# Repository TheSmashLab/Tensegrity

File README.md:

# Tensegrity
All code and any additional documents regarding research in the Tensegrity projects

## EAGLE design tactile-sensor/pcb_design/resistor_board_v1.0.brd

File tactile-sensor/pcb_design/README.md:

# Overview

This project was made by members of the Robotics and Dynamics Lab at Brigham Young University. This directory contains all of the necessary instructions and files for the custom PCB's we designed for reading force data from up to eight 16x64 fabric tactile sensor arrays (or a total of 8192 force readings) at up to 80sps. These boards, in combination with an Arduino Due, enable the use of ROS to read large amounts of tactile data.

These PCBs were designed using Autodesk EAGLE, then later using Fusion 360. The corresponding board, and schematic files are found in this directory, as well as the CAM outputs. These are easy enough to import into Fusion 360.

We used JLCPCB to print out PCBs.

There are three pcbs in this directory: a tactile sensor master board that is a shield for the Arduino Due, a tactile sensor slave board that is mounted next to and attached to each 16x64 sleeve sensor array, and a resistor board that is an add-on to the slave board.
To understand the design behind these PCB's, espessially the slave PCB which is the most technical, I suggest reading the Tactile_Sleeve_Notes.pdf file in the resources folder.

---
# Tactile Sensor Master Board

## Bill of Materials for each Board

| Qty |  Cost  | Device                          | Parts                                                   | Description                                 | PURCHASE_URL |
|-----|--------|---------------------------------|---------------------------------------------------------|---------------------------------------------|--------------|
| 2   | $0.10  | 3-pin Male Header               | SV1, SV2                                                | Decide termination and power source         | NA           |
| 1   | $0.20  | 5-pin Female Header             | SV3                                                     | Plug in external 3.3V buck converter        | NA          |
| NA  | $1.00  | Male Header Pins                |                                                         | Headers needed to put the shield on the due | NA          |
| 8   | $0.35  | 2-pin Male Molex Connector      | CS1, CS2, CS3, CS4, CS5, CS6, CS7, CS8                  | For CS pins                                 | [link](https://www.mouser.com/ProductDetail/Molex/171856-0002?qs=s7UCm7gO1bYKeEMrirBzyw%3D%3D)             |
| 1   | $4.95  | 8-pin Dip Switch                | J1                                                      | Dip switch for selecting sleeve to read     | [link](https://www.mouser.com/ProductDetail/Omron-Electronics/A6E-8104-N?qs=vyIerDHf/mloJqQ30NZRaQ%3D%3D)             |
| 2   | $1.00  | Ethernet port                   | CHAIN_1, CHAIN_2                                        | Used for daisy-chaining slave devices       | [link](https://www.mouser.com/ProductDetail/TE-Connectivity-AMP/5555164-4?qs=BcfjnG7NVaVPSt3aHUi1SQ%3D%3D)           |
| 1   | $1.02  | 200 Ohm Potentiometer           | R1                                                      | Used for terminating data line              | [link](https://www.mouser.com/ProductDetail/Bourns/3362P-1-201LF?qs=sGAEpiMZZMtC25l1F4XBU4KpuikCFD1JVjzxlorewD8%3D)              |
| 1   | $15.95 | External 3.3V Buck Converter    |                                                         | Powers all of the sensors                   | [link](https://www.pololu.com/product/3781)             |

The total price per board (including printing the pcb) is about $40 (parts are $28.02 and JLCPCB charges about $20 for 5 copies of the pcb, plus shipping and tax). Note that there are fairly significant bulk discounts for many of these parts. 

## Schematic

NOTE: there is a PDF version of the schematic in this directory if greater resolution is needed.

## Layout

## Setup

There are a few things that you can physically change on this board. First, the 8-channel dip switch is used to tell the arduino which sensors it should report. If the arduino due is running the tactile_sensors_reporter.ino file, it will read which switches are flipped on and only report the sensors that correspond to those switches. The slave select pins that correspond to each switch are labelled (CS1, CS2, etc.). Use a wire to connect the correct CS pin on the master to the SS pin on the slave device.

Second, there are three male header pins next to the data termination potentimeter. The data line should be terminated using the potentiometer set to 120 ohms (or a tuned value) if only one chain is being used. If both chains are being used, then the line should not be terminated.

Lastly, there is another set of three male header pins with the words EXT and ARD. This will determine if you want to power the sensors from the external buck converter or the arduino. Only power up to two sensors using the arduino. In any other case, use the external buck converter.

---
# Tactile Sensor Slave Board with Add-on Board

## Bill of Materials

| Qty | Cost  | Device                     | Parts                                                       | Description                                   | Purchase Link                                                                                                                                                                                                                                                                                                                                                                                                                                             |
|-----|-------|----------------------------|-------------------------------------------------------------|-----------------------------------------------|-----------------------------------------------------------------------------------------------------------------------------------------------------------------------------------------------------------------------------------------------------------------------------------------------------------------------------------------------------------------------------------------------------------------------------------------------------------|
| 5   | $0.89 | 16-channel Analog Mux      | CMUX, AMUX_1, AMUX_2, AMUX_3, AMUX_4                        | Multiplexers for switching between sensors    | [link](https://www.mouser.com/ProductDetail/Texas-Instruments/CD74HC4067SM96?qs=JHHQeKcAU3DyfvAOSRLjhQ%3D%3D)                                                                                                                                                                                                                                                                                                                                                                                                                                                          |
| 1   | $0.96 | 4-channel Analog Mux       | AMUX_0                                                      | Multiplexer for switching between sensors     | [link](https://www.mouser.com/ProductDetail/Texas-Instruments/TMUX1204DGSR?qs=EBDBlbfErPw42Q0DdvAwUg%3D%3D) |
| 1   | $12.76| SPI-enabled 12-bit ADC     | ADC                                                         | ADC for reading voltage divider               | [link](https://www.mouser.com/ProductDetail/Analog-Devices-Maxim-Integrated/MAX11103AUB%2b?qs=mzcOS1kGbgdW3dlgSnprJw%3D%3D) |
| 1   | $1.38 | 12-bit Binary Counter      | SW                                                          | Counter for triggering MUX's based on clock   | [link](https://www.mouser.com/ProductDetail/Texas-Instruments/SN74LV4040AD?qs=UG/8xqv/6WeL19NQ6cIFrg%3D%3D) |
| 2   | $1.00 | Ethernet port              | INPUT, OUTPUT                                               | Connection for daisy-chain                    | [link](https://www.mouser.com/ProductDetail/TE-Connectivity-AMP/5555164-4?qs=BcfjnG7NVaVPSt3aHUi1SQ%3D%3D) |
| 4   | $0.60 | 2x8-pin Male Header        | ASEL_1, ASEL_2, ASEL_3, ASEL_4                              | For plugging in fabric sensor ribbon cable    | [link](https://www.mouser.com/ProductDetail/Amphenol-FCI/67996-416HLF?qs=zDLUbuhEZ18YJlcRJvn0zg%3D%3D) |
| 1   | $1.86 | 2x8-pin Long Male Header   | CSEL                                                        | For plugging in fabric sensor ribbon cable    | [link](https://www.mouser.com/ProductDetail/Samtec/HTSW-108-10-T-D?qs=%252BZP6/%252BtExtB9K2tO%252BdFStQ%3D%3D) |
| 3   | $0.28 | SPI-enabled 12-bit ADC     | SV1, SV2, ADC_SEL                                           | Turn on termination and choose ADC channel    | [link](https://www.mouser.com/ProductDetail/Amphenol-FCI/68000-403H?qs=eanFghet1JNqC/0Iz%252BuUPw%3D%3D) |
| 3   | $1.02 | 200 Ohm Potentiometer      | R1, R2, R5                                                  | Used for terminating communication lines      | [link](https://www.mouser.com/ProductDetail/Bourns/3362P-1-201LF?qs=sGAEpiMZZMtC25l1F4XBU4KpuikCFD1JVjzxlorewD8%3D)              |
| 1   | $0.89 | 3k Ohm Potentiometer       | R4                                                          | Used as the know half of the voltage divider  | [link](https://www.mouser.com/ProductDetail/Bourns/3362P-1-302LF?qs=sGAEpiMZZMtC25l1F4XBUxCk7s1FufIVD8TlfNkTc8c%3D) |
| 1   | $0.36 | 2-pin Male Molex Connector | SS                                                          | Connection for CS on slave                    | [link](https://www.mouser.com/ProductDetail/Molex/171857-0002?qs=vOeJqewp7jDZ/eRg0MxvZQ%3D%3D) |
| 10  | $0.29 | Blue 3.3V LED              | LED1, LED2, LED3, LED4, LED5, LED6, LED7, LED8, LED9, LED10 | Used to debug clock, display current sensor   | [link](https://www.mouser.com/ProductDetail/Stanley-Electric/VCDB1112H-5AY3B-TR?qs=byeeYqUIh0NdrgXR4WHsww%3D%3D) |
| 1   | $1.99 | Green 3.3V LED             | LED11                                                       | Indicates that the board has power            | [link](https://www.mouser.com/ProductDetail/Lumex/SML-LX0805UPGC-TR?qs=nsAcsc0rFlwqqwNCsw8Xxg%3D%3D) |
| 1   | $0.67 | 10uF Capacitor             | C2                                                          | Used for input to ADC power supply            | [link](https://www.mouser.com/ProductDetail/TDK/C2012X7S1E106K125AE?qs=P1JMDcb91o5L0SBQ9NWlYQ%3D%3D) |
| 16  | $0.27 | 27 Ohm 1W Resistor         | (Add-on)                                                    | Used as pull-down resistor on rows            | [link](https://www.walmart.com/ip/Metal-Film-Resistors-27-Ohm-1W-1-Tolerances-5Color-Bands-Pack-of-30/513536791?wmlspartner=wlpa&selectedSellerId=571) |
| 1   | $2.18 | 2x8-pin Female Headers     | (Add-on)                                                    | Used to connect to main slave board           | [link](https://www.mouser.com/ProductDetail/Samtec/SSQ-108-01-T-D?qs=rU5fayqh%252BE3zRJ1c1JB7Dw%3D%3D) |

Total cost of this board with the add-on is about $55. (parts are about $43.02 and JLCPCB charges about $20 for 10 copies of each pcb, plus shipping and tax).

## Main Schematic

NOTE: there is a PDF version of the schematic in this directory if greater resolution is needed.

## Main Layout

## Add-on Schematic

## Add-on Layout

NOTE: the extra ground pin on the add-on board should be connected to the ground on the main slave board. I have usually done this by soldering a wire directly between the extra ground pin and the labelled ground via hole on the main board.

## Setup

There are a few things that you can physically change on the main slave board. First, the SPI Clock and Counter pins can be terminated with potentiometers. The termination resistors should only be enabled if the board is the last board on the daisy chain. If there are two chains, both ends should be terminated. If used, these should be set to 120 ohms or tuned until the communication channel works. 

Second, there are two ADC channels, both of which read the sensors voltage. There are three male header pins that can be used to enable either of the ADC channels. This should not matter, unless one channel is somehow broken (very unlikely).

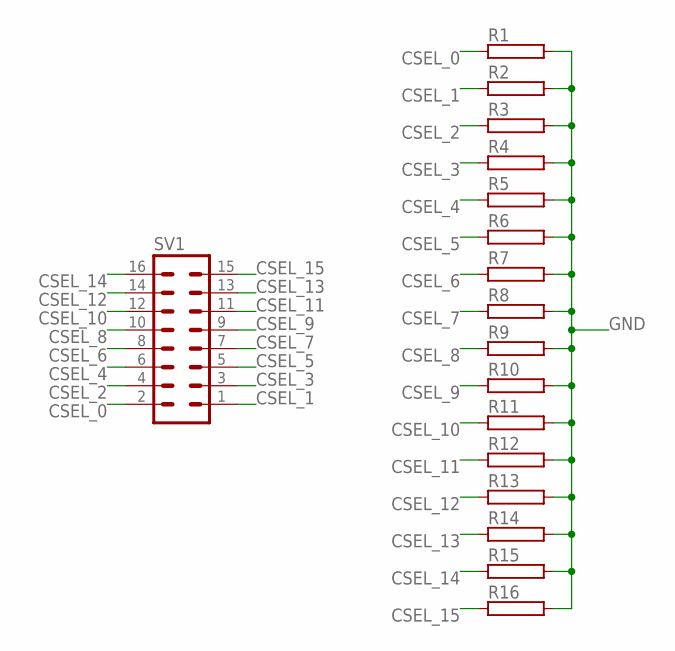
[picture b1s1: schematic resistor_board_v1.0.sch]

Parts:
R1, R2, R3, R4, R5, R6, R7, R8, R9, R10, R11, R12, R13, R14, R15, R16: RHPS58; HPS58
SV1: MA08-2

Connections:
CSEL_0: R1.1, SV1.2
CSEL_1: R2.1, SV1.1
CSEL_2: R3.1, SV1.4
CSEL_3: R4.1, SV1.3
CSEL_4: R5.1, SV1.6
CSEL_5: R6.1, SV1.5
CSEL_6: R7.1, SV1.8
CSEL_7: R8.1, SV1.7
CSEL_8: R9.1, SV1.10
CSEL_9: R10.1, SV1.9
CSEL_10: R11.1, SV1.12
CSEL_11: R12.1, SV1.11
CSEL_12: R13.1, SV1.14
CSEL_13: R14.1, SV1.13
CSEL_14: R15.1, SV1.16
CSEL_15: R16.1, SV1.15
GND: R1.2, R2.2, R3.2, R4.2, R5.2, R6.2, R7.2, R8.2, R9.2, R10.2, R11.2, R12.2, R13.2, R14.2, R15.2, R16.2

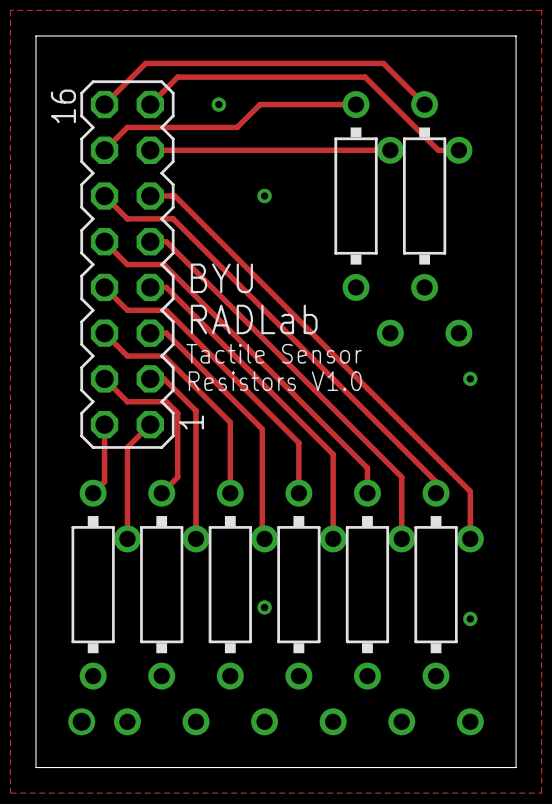
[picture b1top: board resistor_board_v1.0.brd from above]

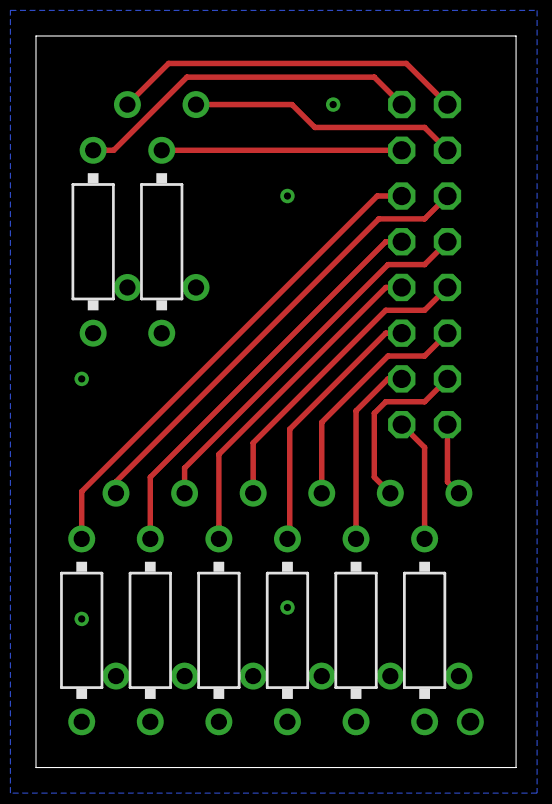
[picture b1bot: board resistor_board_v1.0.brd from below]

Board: 2 copper layers, 26.7 x 40.6 mm, 17 parts (8 on the bottom side), 17 nets.

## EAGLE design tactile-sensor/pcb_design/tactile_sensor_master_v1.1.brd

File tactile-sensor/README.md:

# What is this repository?
This repository contains all of the designs, code, and instructions needed to create a scalable tacile sensor reporting system capable of measuring up to eight 16x64 tactile sensor arrays at 80sps. This sensor system was designed with scale, speed, and cost in mind. The materials to create eight sensors costs less than $1000. However, the piezoresistive fabric used to make the sensors themselves is no longer made. That is a serious limiting factor for future use. Replacements such as [velostat](https://www.adafruit.com/product/1361) could be explored or a [custom](https://hackaday.io/project/168380-polysense) fabric could be made. The design of the system is rather technical, so this repository attempts to explain how the boards function and should be used. A high-level diagram of the sensing system is shown here:

# How is it organized?

This repository is a ROS package designed to be placed in a ROS workspace on the computer connected via USB to the Arduino Due. It can also be placed in the ROS workspace of a computer on the same network for debuging purposes. There are, however, several other directories not needed for a ROS package:

* **pcb_design** - this directory contains all of the wiring diagrams and PCB schematics. Information on purchasing the parts to populate the PCB's is also found here.
* **fabric_sensors** - this directory contains a tutorial on making a 16x64 fabric tactile sensor array along with Solidworks and DXF files used to make various sensors.
* **arduino** - this directory contains the instructions and code needed to test the PCB's and the main file for reporting tacitle data to a computer over USB.

# How do I get set up?

1. Order and populate a single master board. Use the tactile_sensor_master_v1.1_gerber.zip file to order the PCB from any repuable manufacturer and order all the parts listed in the **pcb_design** repository.

2. Order and populate however many slave sensor boards and add-on resistor boards needed (one each per 16x64 fabric sensor). Use tactile_sensor_slave_v2.1_gerber.zip and resitor_board_v1.0_gerber.zip files.

3. Make however many fabric tactile sensor grids you need using the tutorial found in the **fabric_sensors** directory.

4. Test all sensor boards and sensors using the testing scripts found in the **arduino** repository

5. Connect all of the slave boards to the master by first, daisychaining them together using Cat5 cable, and second, connecting each chip select pin indivitually from each slave to the master board.

6. Connect each sensor to its corresponding sensor slave board using the ribbon cables. The **fabric_sensors** repository outlines how these should be connected.

7. Make sure all settings on the board are correct. This includes termination resistors, ADC channel selection, power source selection, and CS dip switches.

8. Connect the Arduino Duo to power and a computer. The computer should be connected to the Due via its native USB port and not its programming port.

9. Run "roscore" on the master computer of your ROS network.

10. On the local computer (either directly or over SSH), launch the desired repeater launch file such as "roslaunch tactile_repeater.launch". The desired topics will now be published to on the ROS network.

11. Calibrate the sensors using the calibrate.py script in the **src/calibration** directory.

12. On any computer on the local ROS network, run "python3 tactile_plotter.py" when inside the **src** directory to plot a sensor's output. The topic that is being plotted can be changed using command line arguments like in this example where "python3 tactile_plotter.py right 3 large_1" will plot the data being published to topic /tactile/right/3 using the calibration file calibration_large_1.yaml.

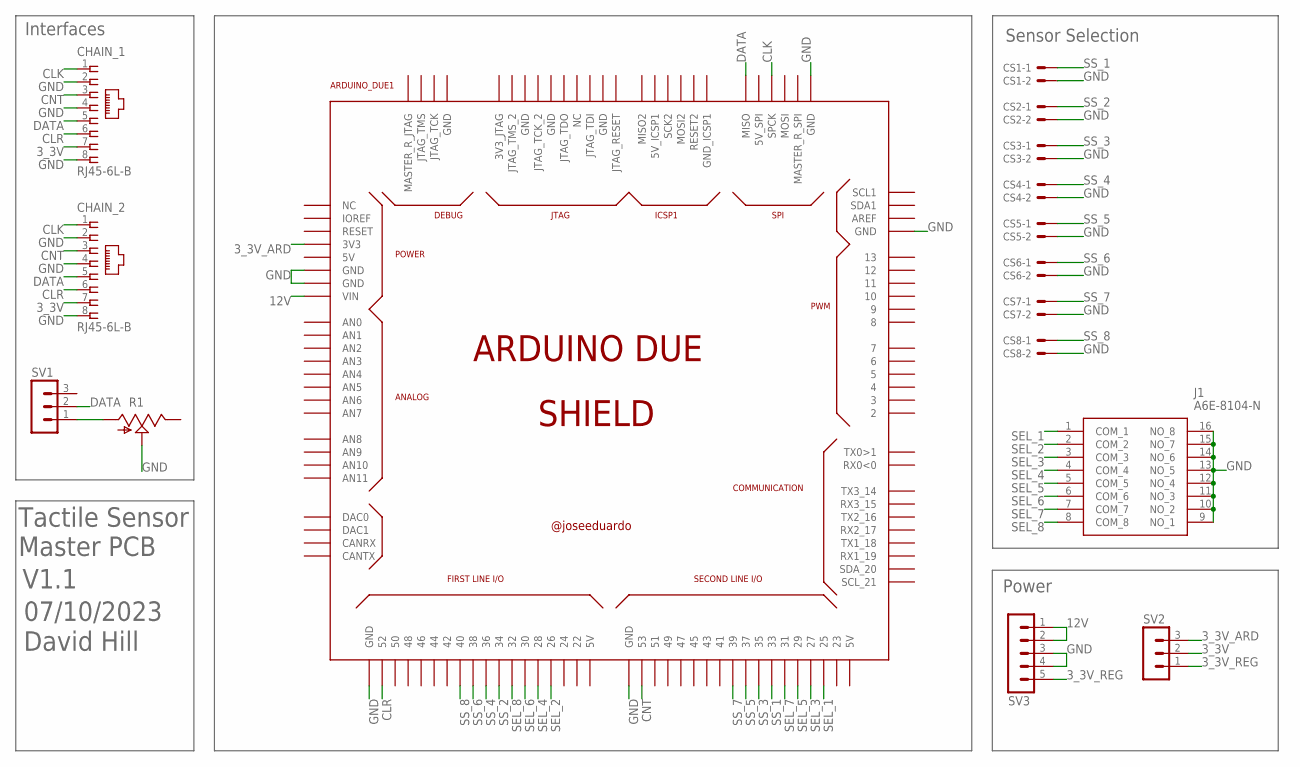
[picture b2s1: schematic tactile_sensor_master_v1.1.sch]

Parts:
ARDUINO_DUE1: ARDUINO_DUE_SHIELD
CHAIN_1, CHAIN_2: RJ45-6L-B; RJ45-NO-SHIELD
CS1, CS2, CS3, CS4, CS5, CS6, CS7, CS8: 22-23-2021
J1: A6E-8104-N; A6E8104N
R1: TRIM_US-B25P; B25P
SV1, SV2: MA03-1
SV3: MA05-1

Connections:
3_3V: CHAIN_1.7, CHAIN_2.7, SV2.2
3_3V_ARD: ARDUINO_DUE1.3V3, SV2.3
3_3V_REG: SV2.1, SV3.5
12V: ARDUINO_DUE1.VIN, SV3.1, SV3.2
CLK: ARDUINO_DUE1.SPCK, CHAIN_1.1, CHAIN_2.1
CLR: ARDUINO_DUE1.52, CHAIN_1.6, CHAIN_2.6
CNT: ARDUINO_DUE1.53, CHAIN_1.3, CHAIN_2.3
DATA: ARDUINO_DUE1.MISO, CHAIN_1.5, CHAIN_2.5, SV1.2
GND: ARDUINO_DUE1.GND, ARDUINO_DUE1.GND_1 (GND), ARDUINO_DUE1.GND_2 (GND), ARDUINO_DUE1.GND_3 (GND), ARDUINO_DUE1.GND_4 (GND), ARDUINO_DUE1.GND_5 (GND), CHAIN_1.2, CHAIN_1.4, CHAIN_1.8, CHAIN_2.2, CHAIN_2.4, CHAIN_2.8, CS1.2, CS2.2, CS3.2, CS4.2, CS5.2, CS6.2, CS7.2, CS8.2, J1.9 (NO_1), J1.10 (NO_2), J1.11 (NO_3), J1.12 (NO_4), J1.13 (NO_5), J1.14 (NO_6), J1.15 (NO_7), J1.16 (NO_8), R1.S, SV3.3, SV3.4
unnamed: R1.A, SV1.1
SEL_1: ARDUINO_DUE1.25, J1.1 (COM_1)
SEL_2: ARDUINO_DUE1.26, J1.2 (COM_2)
SEL_3: ARDUINO_DUE1.27, J1.3 (COM_3)
SEL_4: ARDUINO_DUE1.28, J1.4 (COM_4)
SEL_5: ARDUINO_DUE1.29, J1.5 (COM_5)
SEL_6: ARDUINO_DUE1.30, J1.6 (COM_6)
SEL_7: ARDUINO_DUE1.31, J1.7 (COM_7)
SEL_8: ARDUINO_DUE1.32, J1.8 (COM_8)
SS_1: ARDUINO_DUE1.33, CS1.1
SS_2: ARDUINO_DUE1.34, CS2.1
SS_3: ARDUINO_DUE1.35, CS3.1
SS_4: ARDUINO_DUE1.36, CS4.1
SS_5: ARDUINO_DUE1.37, CS5.1
SS_6: ARDUINO_DUE1.38, CS6.1
SS_7: ARDUINO_DUE1.39, CS7.1
SS_8: ARDUINO_DUE1.40, CS8.1

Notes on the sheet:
Power
Interfaces
Sensor Selection
David Hill
Tactile Sensor Master PCB
V1.1
07/10/2023

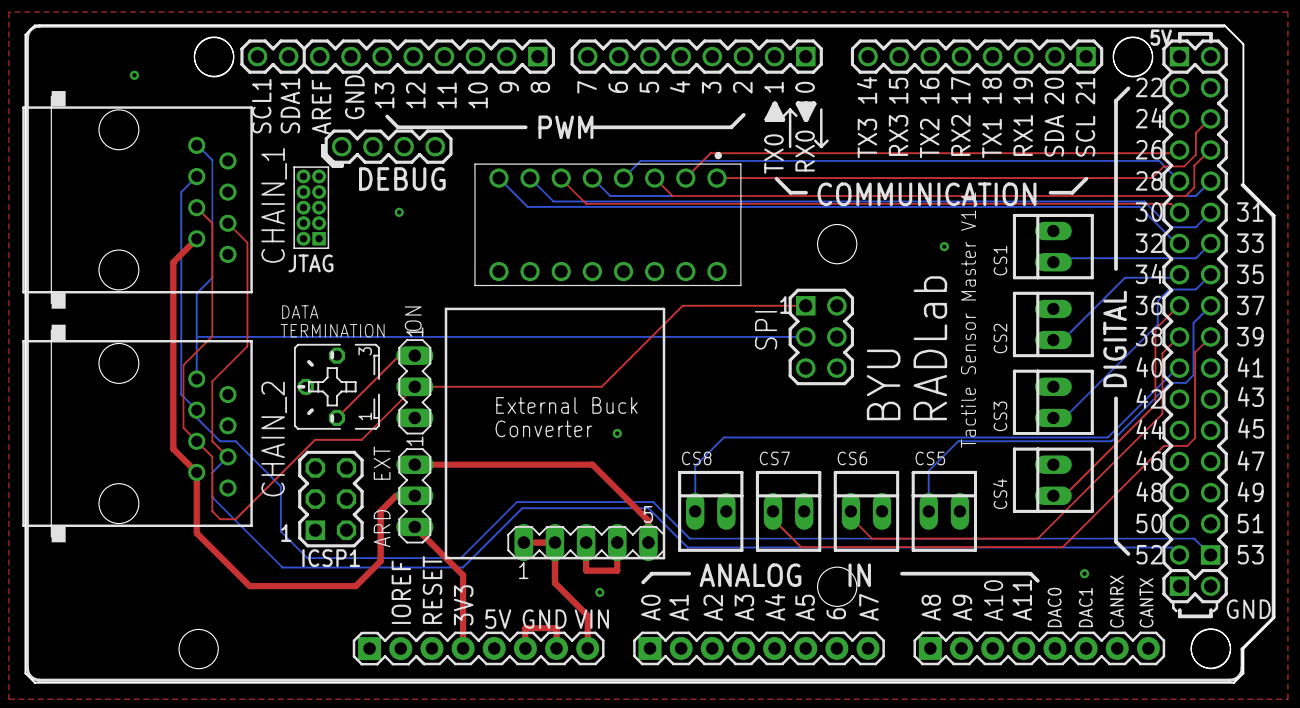
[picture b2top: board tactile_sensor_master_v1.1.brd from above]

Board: 2 copper layers, 101.9 x 53.6 mm, 16 parts (0 on the bottom side), 26 nets.

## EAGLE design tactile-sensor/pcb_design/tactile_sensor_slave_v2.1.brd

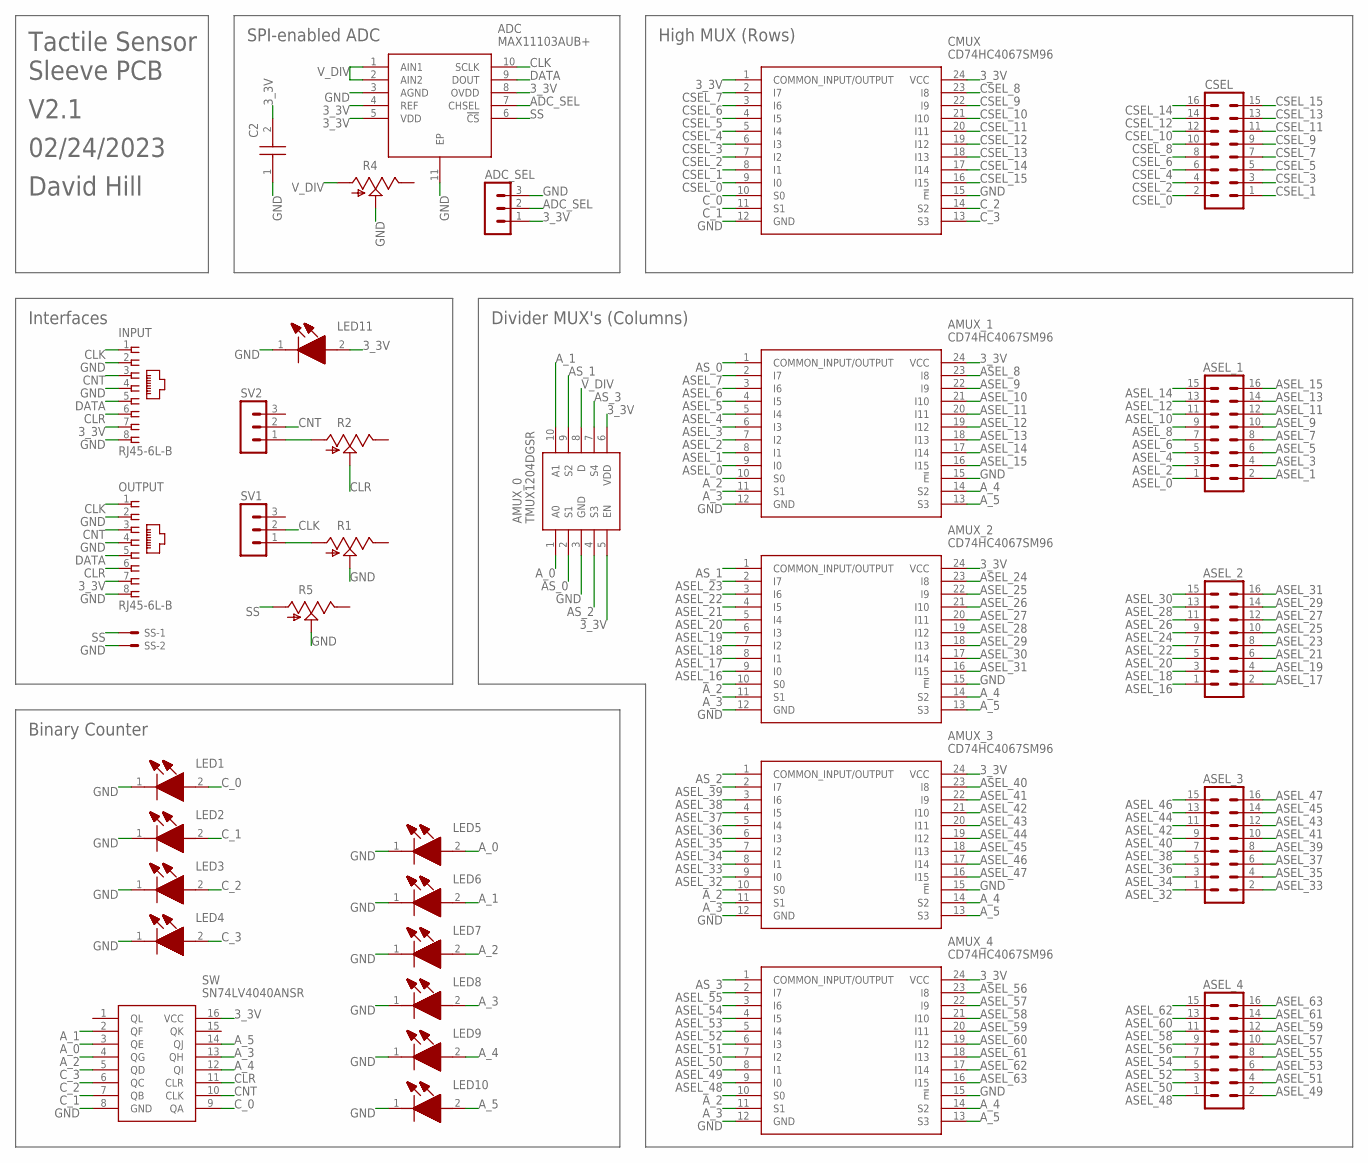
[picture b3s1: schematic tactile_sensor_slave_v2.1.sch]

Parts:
ADC: MAX11103AUB+; SOP50P490X110-11N
ADC_SEL: MA03-1
AMUX_0: TMUX1204DGSR; SOP50P490X110-10N
AMUX_1, AMUX_2, AMUX_3, AMUX_4: CD74HC4067SM96; SOP65P780X200-24N
ASEL_1, ASEL_2, ASEL_3, ASEL_4: MA08-2
C2: C2012X7S1E106K125AE; C2012_COMMERCIAL
CMUX: CD74HC4067SM96; SOP65P780X200-24N
CSEL: MA08-2
INPUT: RJ45-6L-B; RJ45-NO-SHIELD
LED1, LED2, LED3, LED4, LED5, LED6, LED7, LED8, LED9, LED10, LED11: APHCM2012QBC_D-F01; APHCM2012QBCDF01
OUTPUT: RJ45-6L-B; RJ45-NO-SHIELD
R1, R2, R4, R5: TRIM_US-B25P; B25P
SS: 22-23-2021
SV1, SV2: MA03-1
SW: SN74LV4040ANSR; SOIC127P780X200-16N

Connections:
3_3V: ADC.4 (REF), ADC.5 (VDD), ADC.8 (OVDD), ADC_SEL.1, AMUX_0.5 (EN), AMUX_0.6 (VDD), AMUX_1.24 (VCC), AMUX_2.24 (VCC), AMUX_3.24 (VCC), AMUX_4.24 (VCC), C2.2, CMUX.1 (COMMON_INPUT/OUTPUT), CMUX.24 (VCC), INPUT.7, LED11.2 (A), OUTPUT.7, SW.16 (VCC)
ADC_SEL: ADC.7 (CHSEL), ADC_SEL.2
ASEL_0: AMUX_1.9 (I0), ASEL_1.1
ASEL_1: AMUX_1.8 (I1), ASEL_1.2
ASEL_2: AMUX_1.7 (I2), ASEL_1.3
ASEL_3: AMUX_1.6 (I3), ASEL_1.4
ASEL_4: AMUX_1.5 (I4), ASEL_1.5
ASEL_5: AMUX_1.4 (I5), ASEL_1.6
ASEL_6: AMUX_1.3 (I6), ASEL_1.7
ASEL_7: AMUX_1.2 (I7), ASEL_1.8
ASEL_8: AMUX_1.23 (I8), ASEL_1.9
ASEL_9: AMUX_1.22 (I9), ASEL_1.10
ASEL_10: AMUX_1.21 (I10), ASEL_1.11
ASEL_11: AMUX_1.20 (I11), ASEL_1.12
ASEL_12: AMUX_1.19 (I12), ASEL_1.13
ASEL_13: AMUX_1.18 (I13), ASEL_1.14
ASEL_14: AMUX_1.17 (I14), ASEL_1.15
ASEL_15: AMUX_1.16 (I15), ASEL_1.16
ASEL_16: AMUX_2.9 (I0), ASEL_2.1
ASEL_17: AMUX_2.8 (I1), ASEL_2.2
ASEL_18: AMUX_2.7 (I2), ASEL_2.3
ASEL_19: AMUX_2.6 (I3), ASEL_2.4
ASEL_20: AMUX_2.5 (I4), ASEL_2.5
ASEL_21: AMUX_2.4 (I5), ASEL_2.6
ASEL_22: AMUX_2.3 (I6), ASEL_2.7
ASEL_23: AMUX_2.2 (I7), ASEL_2.8
ASEL_24: AMUX_2.23 (I8), ASEL_2.9
ASEL_25: AMUX_2.22 (I9), ASEL_2.10
ASEL_26: AMUX_2.21 (I10), ASEL_2.11
ASEL_27: AMUX_2.20 (I11), ASEL_2.12
ASEL_28: AMUX_2.19 (I12), ASEL_2.13
ASEL_29: AMUX_2.18 (I13), ASEL_2.14
ASEL_30: AMUX_2.17 (I14), ASEL_2.15
ASEL_31: AMUX_2.16 (I15), ASEL_2.16
ASEL_32: AMUX_3.9 (I0), ASEL_3.1
ASEL_33: AMUX_3.8 (I1), ASEL_3.2
ASEL_34: AMUX_3.7 (I2), ASEL_3.3
ASEL_35: AMUX_3.6 (I3), ASEL_3.4
ASEL_36: AMUX_3.5 (I4), ASEL_3.5
ASEL_37: AMUX_3.4 (I5), ASEL_3.6
ASEL_38: AMUX_3.3 (I6), ASEL_3.7
ASEL_39: AMUX_3.2 (I7), ASEL_3.8
ASEL_40: AMUX_3.23 (I8), ASEL_3.9
ASEL_41: AMUX_3.22 (I9), ASEL_3.10
ASEL_42: AMUX_3.21 (I10), ASEL_3.11
ASEL_43: AMUX_3.20 (I11), ASEL_3.12
ASEL_44: AMUX_3.19 (I12), ASEL_3.13
ASEL_45: AMUX_3.18 (I13), ASEL_3.14
ASEL_46: AMUX_3.17 (I14), ASEL_3.15
ASEL_47: AMUX_3.16 (I15), ASEL_3.16
ASEL_48: AMUX_4.9 (I0), ASEL_4.1
ASEL_49: AMUX_4.8 (I1), ASEL_4.2
ASEL_50: AMUX_4.7 (I2), ASEL_4.3
ASEL_51: AMUX_4.6 (I3), ASEL_4.4
ASEL_52: AMUX_4.5 (I4), ASEL_4.5
ASEL_53: AMUX_4.4 (I5), ASEL_4.6
ASEL_54: AMUX_4.3 (I6), ASEL_4.7
ASEL_55: AMUX_4.2 (I7), ASEL_4.8
ASEL_56: AMUX_4.23 (I8), ASEL_4.9
ASEL_57: AMUX_4.22 (I9), ASEL_4.10
ASEL_58: AMUX_4.21 (I10), ASEL_4.11
ASEL_59: AMUX_4.20 (I11), ASEL_4.12
ASEL_60: AMUX_4.19 (I12), ASEL_4.13
ASEL_61: AMUX_4.18 (I13), ASEL_4.14
ASEL_62: AMUX_4.17 (I14), ASEL_4.15
ASEL_63: AMUX_4.16 (I15), ASEL_4.16
AS_0: AMUX_0.2 (S1), AMUX_1.1 (COMMON_INPUT/OUTPUT)
AS_1: AMUX_0.9 (S2), AMUX_2.1 (COMMON_INPUT/OUTPUT)
AS_2: AMUX_0.4 (S3), AMUX_3.1 (COMMON_INPUT/OUTPUT)
AS_3: AMUX_0.7 (S4), AMUX_4.1 (COMMON_INPUT/OUTPUT)
A_0: AMUX_0.1 (A0), LED5.2 (A), SW.3 (QE)
A_1: AMUX_0.10 (A1), LED6.2 (A), SW.2 (QF)
A_2: AMUX_1.10 (S0), AMUX_2.10 (S0), AMUX_3.10 (S0), AMUX_4.10 (S0), LED7.2 (A), SW.4 (QG)
A_3: AMUX_1.11 (S1), AMUX_2.11 (S1), AMUX_3.11 (S1), AMUX_4.11 (S1), LED8.2 (A), SW.13 (QH)
A_4: AMUX_1.14 (S2), AMUX_2.14 (S2), AMUX_3.14 (S2), AMUX_4.14 (S2), LED9.2 (A), SW.12 (QI)
A_5: AMUX_1.13 (S3), AMUX_2.13 (S3), AMUX_3.13 (S3), AMUX_4.13 (S3), LED10.2 (A), SW.14 (QJ)
CLK: ADC.10 (SCLK), INPUT.1, OUTPUT.1, SV1.2
CLR: INPUT.6, OUTPUT.6, R2.S, SW.11 (CLR)
CNT: INPUT.3, OUTPUT.3, SV2.2, SW.10 (CLK)
CSEL_0: CMUX.9 (I0), CSEL.2
CSEL_1: CMUX.8 (I1), CSEL.1
CSEL_2: CMUX.7 (I2), CSEL.4
CSEL_3: CMUX.6 (I3), CSEL.3
CSEL_4: CMUX.5 (I4), CSEL.6
CSEL_5: CMUX.4 (I5), CSEL.5
CSEL_6: CMUX.3 (I6), CSEL.8
CSEL_7: CMUX.2 (I7), CSEL.7
CSEL_8: CMUX.23 (I8), CSEL.10
CSEL_9: CMUX.22 (I9), CSEL.9
CSEL_10: CMUX.21 (I10), CSEL.12
CSEL_11: CMUX.20 (I11), CSEL.11
CSEL_12: CMUX.19 (I12), CSEL.14
CSEL_13: CMUX.18 (I13), CSEL.13
CSEL_14: CMUX.17 (I14), CSEL.16
CSEL_15: CMUX.16 (I15), CSEL.15
C_0: CMUX.10 (S0), LED1.2 (A), SW.9 (QA)
C_1: CMUX.11 (S1), LED2.2 (A), SW.7 (QB)
C_2: CMUX.14 (S2), LED3.2 (A), SW.6 (QC)
C_3: CMUX.13 (S3), LED4.2 (A), SW.5 (QD)
DATA: ADC.9 (DOUT), INPUT.5, OUTPUT.5
GND: ADC.3 (AGND), ADC.11 (EP), ADC_SEL.3, AMUX_0.3 (GND), AMUX_1.12 (GND), AMUX_1.15 (!E), AMUX_2.12 (GND), AMUX_2.15 (!E), AMUX_3.12 (GND), AMUX_3.15 (!E), AMUX_4.12 (GND), AMUX_4.15 (!E), C2.1, CMUX.12 (GND), CMUX.15 (!E), INPUT.2, INPUT.4, INPUT.8, LED1.1 (K), LED2.1 (K), LED3.1 (K), LED4.1 (K), LED5.1 (K), LED6.1 (K), LED7.1 (K), LED8.1 (K), LED9.1 (K), LED10.1 (K), LED11.1 (K), OUTPUT.2, OUTPUT.4, OUTPUT.8, R1.S, R4.S, R5.S, SS.2, SW.8 (GND)
unnamed: R1.A, SV1.1
unnamed: R2.A, SV2.1
SS: ADC.6 (!CS), R5.A, SS.1
V_DIV: ADC.1 (AIN1), ADC.2 (AIN2), AMUX_0.8 (D), R4.A

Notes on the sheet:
Tactile Sensor Sleeve PCB
V2.1
02/24/2023
David Hill
SPI-enabled ADC
High MUX (Rows)
Divider MUX's (Columns)
Interfaces
Binary Counter

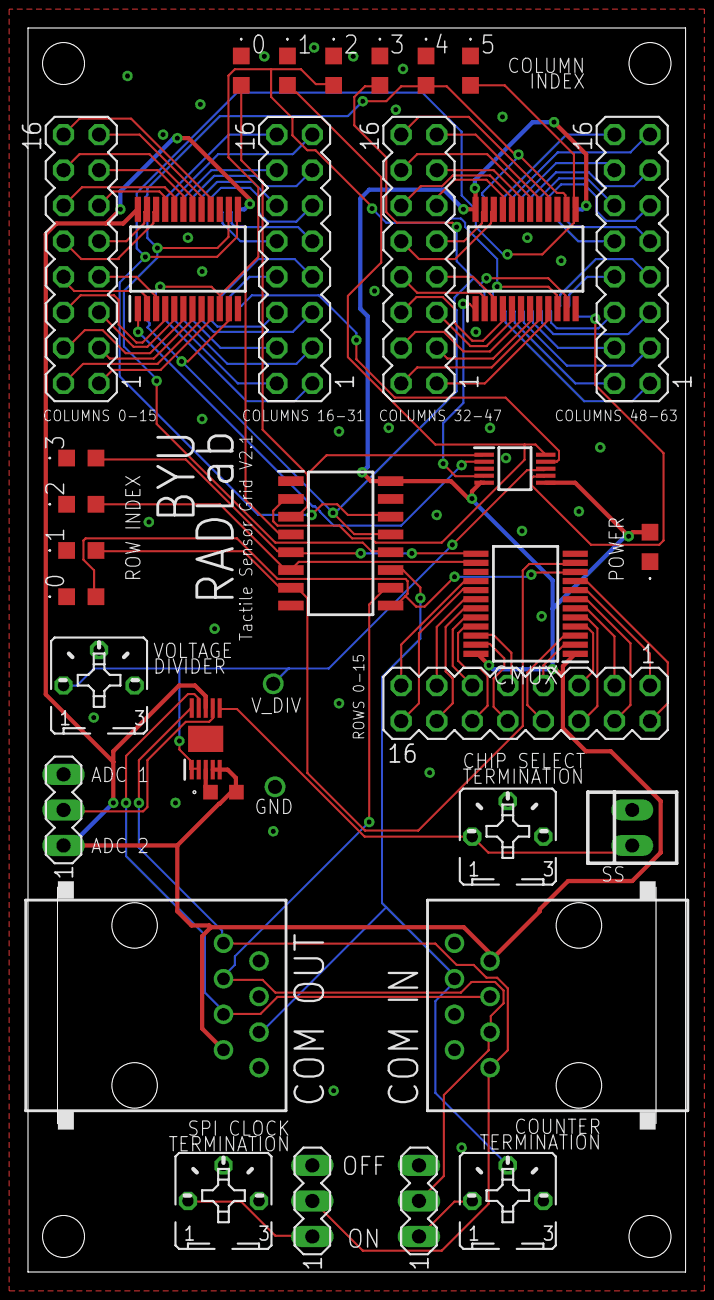
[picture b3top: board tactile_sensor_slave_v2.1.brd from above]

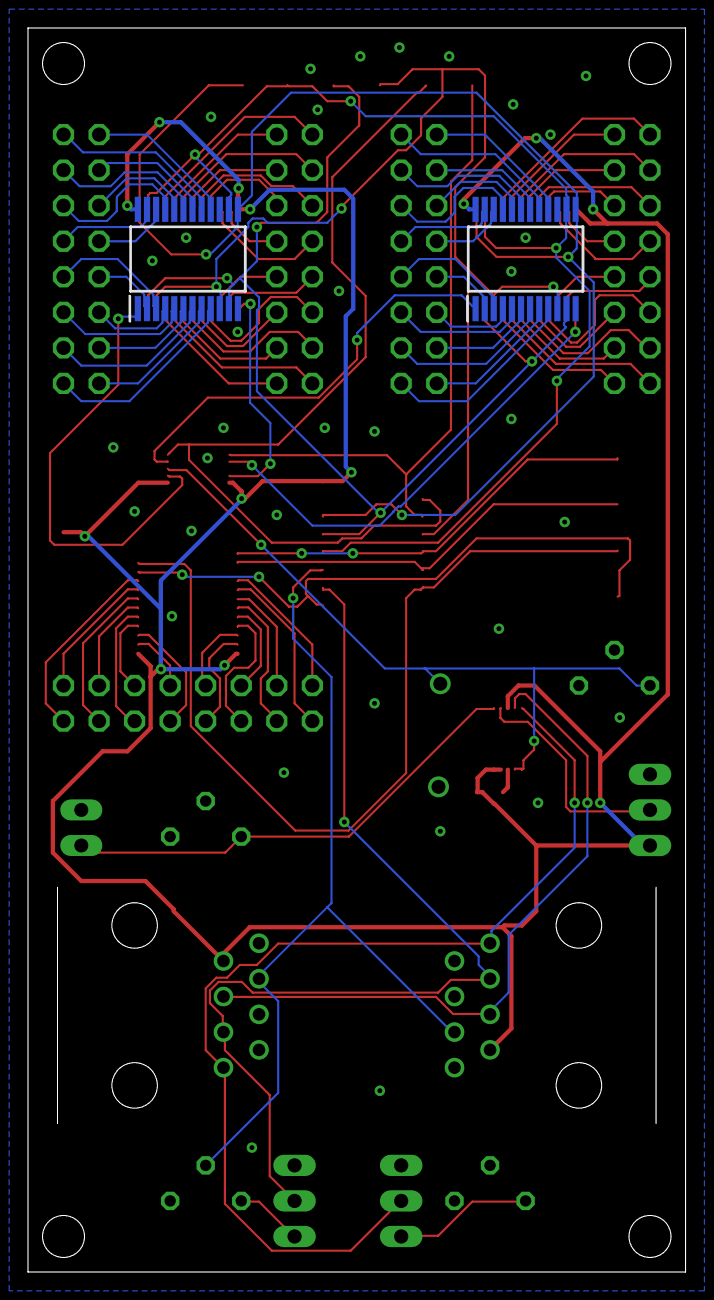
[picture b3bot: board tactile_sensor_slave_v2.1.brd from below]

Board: 2 copper layers, 47.0 x 88.9 mm, 35 parts (2 on the bottom side), 105 nets.

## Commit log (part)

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2024-01-13 Static sim w/o forces
2024-01-22 Add connection type and update YAML parser
2024-01-25 Add Tensegrity class and change_connection_length method
2024-01-25 Add optimization module
2024-03-08 Optimizer working except strings through multiple nodes
2024-03-11 Fix pinning and allow string to pass through multiple nodes
2024-03-11 Temp solution to update tension(force) in each connection
2024-03-11 Update project documentation
2024-03-11 visualization uses dotted line if tension in string is 0
2024-03-21 Update connection forces and optimize simulation
2024-03-21 Update documentation and clean up code
2024-04-03 Added Energy Equations
2024-06-26 feat: Add new box configuration with nodes and connections
2024-07-17 Linked nodes
2024-07-17 Fix bug in 2D simulation after adding linked nodes
2024-07-17 chore: Ignore project-specific figures in .gitignore
2024-07-19 feat: Add surface plotting to visualization
2024-10-02 Separate 2D and 3D 6-box
2024-10-02 Change directory name for code to src
2024-10-18 Update README.md with instructions for installing tkinter on WSL
2025-03-05 Release 1.0.0
2025-03-09 Update README.md to generalize simulation description for Tensegrity structures
2025-03-09 Update README.md for generalization and add installation instructions; create pyproject.toml for packaging
2025-03-10 Update README.md to generalize project title and enhance installation instructions
2025-03-11 Refactor to make dim a property of the Tensegrity Class, update documentation to support
2025-03-14 Update documentation: add UML Class diagrams, move content into content folder
2025-03-14 Add UML class diagrams for data structures and solver; update .gitignore to include plantuml files
2025-03-26 Allow 2.5D Sims to be easier to visualize in 2D. Add another 2.5D sample YAML
2025-03-28 Fix tests
2025-03-28 Update README to reference the new documentation PDF for simulation setup
2025-04-01 Update TensegritySim.pdf with latest simulation details
2025-05-02 Refactor pin settings in YAML files to remove unnecessary values
2026-02-24 Add NonLinProps and ConnectionNonLinear classes for non-linear material properties
2026-02-24 Add Jupyter Notebook for Overture TPU validation and analysis
    - Implemented stress-strain data processing for Overture TPU.
    - Added calculations for linear stiffness and error minimization.
    - Included visualizations for measured vs simulated forces.
    - Developed tensegrity system simulations for Array 1 and Array 3.
    - Integrated error analysis for both arrays to determine optimal stiffness.
2026-02-24 Remove unnecessary newline in OvertureValidation.ipynb
2026-02-24 Add Inner_distance array for validation in Array1.py
2026-02-24 Add stiffness calculations for fishing line, aluminum, and PLA in Stiffnesses.py
2026-02-24 Fix formatting and execution counts in OvertureValidation.ipynb
2026-02-24 Refactor code structure for improved readability and maintainability
2026-02-24 Add Array 3 data file with mass and inner distance measurements
2026-02-27 Fix execution counts in OvertureValidation.ipynb and update Connection initialization to remove 'linear' argument
2026-02-27 Fix class name casing and update import statements in OvertureValidation.ipynb
2026-02-27 Fix execution count in OvertureValidation.ipynb to resolve ImportError for NonlinProps
2026-02-27 Update __init__.py to include NonlinProps and ConnectionNonlinear in imports and __all__ list
2026-02-27 Bump version to 1.0.1 in __init__.py
2026-03-12 Fix execution counts and update RMSE values in OvertureValidation notebook
2026-03-15 Add Bambu TPU sheet_18.csv for validation data
2026-03-15 added sheet 18
2026-03-15 Calculated the correction factor for just Array 8
2026-03-16 Add new dataset for validation: Array 9 with mass and inner distance measurements. Update Array 9 validation code to include nonlinear solver and correction factor.
2026-03-16 Include force vs displacement data for TPU sheets 21--23.
2026-03-20 Created a new Jupyter Notebook for 1 by 2 Bambu analysis.
2026-03-20 Created the stress-strain csv file for Array 18.
2026-03-20 Created the csv file for the second set of data for Array 18.
2026-03-21 Plotted the old and new points of Node 6 as they were measured.
2026-03-26 The 1 by 2 is failing to solve.
2026-03-26 Trying Bond's code update part 1.
2026-03-26 Trying Bond's code part 2.
2026-03-31 Couldn't get the nonlinear solver to work for the 1 by 2 array.
2026-04-02 added files
2026-04-02 added more files
2026-04-02 added new folder
2026-05-28 Add output image file for project visualization
2026-06-04 Added all the changes from the GitLab branch
2026-06-04 Added the validation cylinder yaml file
2026-06-08 Updated the validation yaml to reflect the correct stiffnesses and initial length ratios
2026-06-08 Added a print out of positions of select nodes
2026-06-08 Updated parameters to meet initial positions better.
2026-06-09 Final changes were made for Caleb to finish his thesis.
2026-06-29 made my branch and it works!
2026-06-29 fixed file path in requirments.txt
2026-06-29 Updated to python 3.12.13
